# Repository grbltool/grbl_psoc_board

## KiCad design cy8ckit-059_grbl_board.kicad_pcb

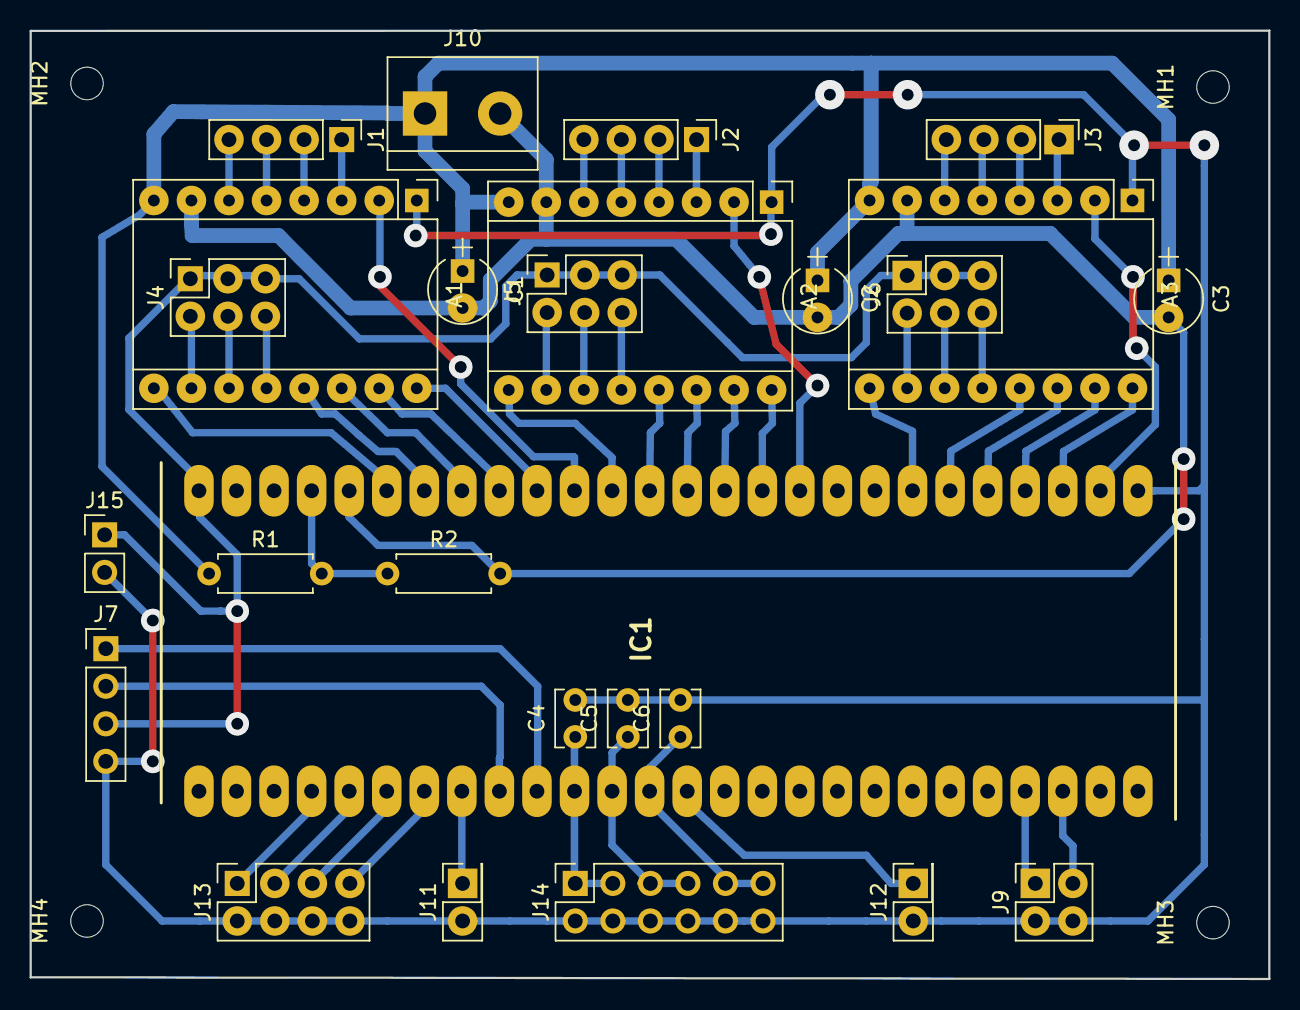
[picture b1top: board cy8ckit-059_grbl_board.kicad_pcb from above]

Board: 2 copper layers, 83.8 x 64.1 mm, 30 parts (0 on the bottom side), 57 nets.

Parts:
A1, A2, A3: Pololu_Breakout_DRV8825; Pololu_Breakout-16_15.2x20.3mm
C1, C2, C3: CP; CP_Radial_Tantal_D4.5mm_P2.50mm
C4, C5, C6: 100nF; C_Disc_D3.8mm_W2.6mm_P2.50mm
IC1: CY8CKIT-059; DIP2032W100P254L6860H700Q52N
J1, J2, J3: Connector:Conn_01x04_Male; Pin_Header_Straight_1x04_Pitch2.54mm
J4, J5, J6: Conn_02x03_Odd_Even; Socket_Strip_Straight_2x03_Pitch2.54mm
J7: Conn_01x04_Male; Socket_Strip_Straight_1x04_Pitch2.54mm
J9: Conn_02x02_Odd_Even; Socket_Strip_Straight_2x02_Pitch2.54mm
J10: Screw_Terminal_01x02; TerminalBlock_bornier-2_P5.08mm
J11, J12: Conn_02x01; Socket_Strip_Straight_2x01_Pitch2.54mm
J13: Conn_02x04_Odd_Even; Socket_Strip_Straight_2x04_Pitch2.54mm
J14: Conn_02x06_Odd_Even; Socket_Strip_Straight_2x06_Pitch2.54mm
J15: Conn_01x02_Male; Socket_Strip_Straight_1x02_Pitch2.54mm
MH1, MH2, MH3, MH4: MountingHole; MountingHole_2.2mm_M2
R1, R2: R; R_Axial_DIN0207_L6.3mm_D2.5mm_P7.62mm_Horizontal

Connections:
+5V: IC1.52, J4.1, J4.3, J4.5, J5.1, J5.3, J5.5, J6.1, J6.3, J6.5, J7.3, J15.1
+36V: A1.8, A2.8, A3.8, C1.1, C2.1, C3.1, J10.1, R1.1
/break: IC1.4, J13.1
/coolant_flood: IC1.23, J9.1
/coolant_mist: IC1.24, J9.3
/cycle_start: IC1.6, J13.5
/dir_x: A1.16, IC1.43
/dir_y: A2.16, IC1.37
/dir_z: A3.16, IC1.29
/enable_x: A1.9, IC1.47
/enable_y: A2.9, IC1.41
/enable_z: A3.9, IC1.33
/fault_x: A1.2, IC1.42
/fault_y: A2.2, IC1.36
/fault_z: A3.2, IC1.28
/feed_hold: IC1.5, J13.3
/limit_x: C4.1, IC1.11, J14.1, J14.3
/limit_y: C5.1, IC1.12, J14.5, J14.7
/limit_z: C6.1, IC1.13, J14.9, J14.11
/motor_voltage: IC1.49, R1.2, R2.1
/probe: IC1.8, J11.1
/reset_x: A1.13, IC1.46
/reset_y: A2.13, IC1.40
/reset_z: A3.13, IC1.32
/safety_door: IC1.7, J13.7
/sleep_x: A1.14, IC1.45
/sleep_y: A2.14, IC1.39
/sleep_z: A3.14, IC1.31
/spindle_pwm: IC1.14, J12.1
/step_x: A1.15, IC1.44
/step_y: A2.15, IC1.38
/step_z: A3.15, IC1.30
/uart_rx: IC1.10, J7.1
/uart_tx: IC1.9, J7.2
GND: A1.7, A2.7, A3.7, C1.2, C2.2, C3.2, IC1.48, J10.2, R2.2
GNDD: A1.1, A2.1, A3.1, C4.2, C5.2, C6.2, IC1.27, J7.4, J9.2, J9.4, J11.2, J12.2, J13.2, J13.4, J13.6, J13.8, J14.2, J14.4, J14.6, J14.8, J14.10, J14.12, J15.2
unnamed: A1.3, J1.1
unnamed: A1.4, J1.2
unnamed: A1.5, J1.3
unnamed: A1.6, J1.4
unnamed: A1.10, J4.2
unnamed: A1.11, J4.4
unnamed: A1.12, J4.6
unnamed: A2.3, J2.1
unnamed: A2.4, J2.2
unnamed: A2.5, J2.3
unnamed: A2.6, J2.4
unnamed: A2.10, J5.2
unnamed: A2.11, J5.4
unnamed: A2.12, J5.6
unnamed: A3.3, J3.1
unnamed: A3.4, J3.2
unnamed: A3.5, J3.3
unnamed: A3.6, J3.4
unnamed: A3.10, J6.2
unnamed: A3.11, J6.4
unnamed: A3.12, J6.6

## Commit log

2019-06-02 V1.0
    - functionality like a arduino grbl board with stepper drivers and spindle pwm
    - this board is for drv8825 drivers
2020-01-07 V2.0
